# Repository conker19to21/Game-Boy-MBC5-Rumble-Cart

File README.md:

# Game Boy MBC5 Cartridge

This is a flashable MBC5-rumble based single cart for the Game Boy.

I had adapted the DC rumble motor to the board to allow the option to have rumble availability. This does NOT make non rumble based games have rumble feedback.

This board allows the option to allow both rumble and non rumble games in 1 cart with full save functionality!

Original files were converted from Eagle to KiCad cleaned and modified to add the changes.

Please note you will require either a Hot Air rework station or Hot Plate heating station to secure the DC motor properly to the board.

The Rumble feature is optional and if you decide not to use it exclude the following:

R2,
R3,
M1,
D1,
Q3

Battery hold down is NOT included however can be aquired at the following 2 links:

<a href="https://oshpark.com/shared_projects/XSjucPvH"> CR2Retainer</a>

<a href="https://www.digikey.com/short/4zrrw5rr"> RETAINER</a>

When installing D1 make sure it is in the correct orientation with diode line inside white boxed outline as seen in photo:

Special Thanks to Bucket Mouse, HDR and Bonzo!

Please see below for the Mouse's original documentation.

![image](https://private-user-images.githubusercontent.com/79350460/362808066-d0c1e5a3-aa70-49f6-8867-7be02a11127e.png?jwt=eyJhbGciOiJIUzI1NiIsInR5cCI6IkpXVCJ9.eyJpc3MiOiJnaXRodWIuY29tIiwiYXVkIjoicmF3LmdpdGh1YnVzZXJjb250ZW50LmNvbSIsImtleSI6ImtleTUiLCJleHAiOjE3MjUxNzgzNjYsIm5iZiI6MTcyNTE3ODA2NiwicGF0aCI6Ii83OTM1MDQ2MC8zNjI4MDgwNjYtZDBjMWU1YTMtYWE3MC00OWY2LTg4NjctN2JlMDJhMTExMjdlLnBuZz9YLUFtei1BbGdvcml0aG09QVdTNC1ITUFDLVNIQTI1NiZYLUFtei1DcmVkZW50aWFsPUFLSUFWQ09EWUxTQTUzUFFLNFpBJTJGMjAyNDA5MDElMkZ1cy1lYXN0LTElMkZzMyUyRmF3czRfcmVxdWVzdCZYLUFtei1EYXRlPTIwMjQwOTAxVDA4MDc0NlomWC1BbXotRXhwaXJlcz0zMDAmWC1BbXotU2lnbmF0dXJlPTA1MjI0NGZjN2M0MmQwMzY3ZTIxMTJkNjZlNmY0YThiMWQ0MDJiY2EwYzVjMDg4ZDA5NmZlMzE5MmU4ZjRjODkmWC1BbXotU2lnbmVkSGVhZGVycz1ob3N0JmFjdG9yX2lkPTAma2V5X2lkPTAmcmVwb19pZD0wIn0.tLwJES8k5k2GEA-q7z0vVUgHWVOFACCc68rWR7xbyPs)

This is my design of a flashable MBC5-based cartridge for the Game Boy. The MBC5 mapper greatly augments the memory access of the Game Boy for larger games. Most of the games that came out in the last years of the Game Boy and Game Boy Color used the MBC5 mapper.

This circuit board should cover most MBC5 games. The features are as follows:

- Able to make games up to 4 MB in size, that use up to 1 Mbit of RAM
- Compatibility with all four of the popular Game Boy battery management ICs - MM1026, MM1134, BA6129, and BA6735
- The option to add battery backup to the cartridge *without* the need of the original battery management ICs - perfect for MBC5 donors that didn't have batteries in them
- Fully compatible with the <a href="https://www.gbxcart.com/">GBxCart RW</a> so you can transfer games and save files to and from the board

All gerbers and source files can be found in this repo, as this project is fully open source. Technical documentation of the board can be found in the Technical folder.

## Important Things Before You Start

1) To use this board, you need to have an original Game Boy game that uses an MBC5 mapper chip. <a href="https://catskull.net/gb-rom-database/">You can find a list of games and their mappers here</a>. Use the search function. Please note the RAM is in bytes, not bits. Since SRAM in this repo is defined in bits, you need to convert by multiplying the number of bytes by 8.
2) You will need to remove the MBC5 from your donor cartridge for use on this board. This will require a hot air rework station or a hot plate. There's a list below of other parts you can re-use from the donor cartridge.
3) When soldering parts on, it's a good idea to put kapton tape or otherwise cover the bottom cartridge edge. You do not want to get solder on the cartridge contacts.
4) I am not responsible for any damage you do to your self or your property. Attempt this project at your own risk.
5) I do not guarantee design compatibility. You may encounter issues with certain games. There is also a chance I have made an error in the design or the BOM - if this is the case, I will do everything I can to address the problem as quickly as possible.
6) If you are using this board to make games other than for personal use, you must have permission from the originator to use and distribute any ROM images or other related material. You are responsible for making sure you adhere to any license requirements.

DO NOT use my circuit boards for profiting from stolen work - this especially includes homebrew content, ROM hacks, and using fan-made labels without permission from the originator. **Support original creators!**

## Board Characteristics and Order Information

The zipped folder contains all the gerber files for this board. The following options **must** be chosen when ordering boards for yourself.

- Thickness: 0.8mm
- Surface Finish: ENIG
- Gold Fingers: Yes, 30° chamfer

You can use the zipped folder at any board fabricator you like.

<a href="https://oshpark.com/shared_projects/T98aCJad">The board is also listed on OSH Park as well.</a> **Be sure to get them in 0.8mm thickness if you order from here.**

## Required Equipment

The EEPROMs on the board needs to be programmed somehow. I recommend using the GBxCart, as mentioned. These boards are fully compatible with it, and it makes reflashing games extremely easy using <a href="https://github.com/lesserkuma/FlashGBX">lesserkuma's FlashGBX software</a>.

Alternatively, you can buy an EEPROM programmer with a TSOP adapter. The downside to this method is that you have to desolder the chip every time you want to program it. The <a href="https://flashcatusb.com/">FlashcatUSB</a> is one popular option in retro spaces.

## Battery Safety

When assembling a board, I recommend populating all the parts *except* the battery, and getting it to run initially without it. This is to make it easier to fix any solder connections that might need fixing, without having to worry about getting the battery hot. And if you need to rework anything near the battery after you've put it on the board, be safe and remove it before putting a hot soldering iron next to it.

And this should go without saying, but if you're assembling these boards with a hot plate or hot air, *do not* solder the battery on this way. You should use an iron, and keep heat off of the battery as much as possible. 

(Also check polarity!)

## Board Configurations

The board comes with five sets of jumper pads for solder bridges. SJ1, SJ2, SJ3, and SJ4 require you to solder bridge the middle pad either to the left or right pads. SJ7 is configured by either leaving the pads unsoldered or bridging them with solder. Here are the situations where you need to add solder bridges.

### SRAM Size Selection (SJ1 and SJ2, or SW1)

These jumpers are located underneath the MBC5 chip, and labeled "64K" and "256K/1M". Solder them to configure the amount of RAM your cart uses. You must configure these pads for every game you make, unless you do not need RAM. <a href="https://catskull.net/gb-rom-database/">You can find a list of games here with their respective RAM sizes.</a>

- If the game you're making uses 256 Kbit or 1 Mbit of RAM, then solder the middle pads of the two jumper sets to the right pads.
- If the game you're making uses 64 Kbit of RAM, then solder the middle pads of the two jumper sets to the left pads.
- SJ1 and SJ2 must be soldered in the same direction.
- The footprint of these selection pads should allow for a DPDT switch, part number CAS-220A1, to be placed on these pads instead of having to bridge the pads with solder.

Note that you can make games that only require 64 Kbit of RAM and still use a 256 Kbit or 1 Mbit SRAM chip. You still need to configure the jumpers to the 64Kb setting, though.

**I recommend using 64 Kbit or 256 Kbit RAM chips, unless you absolutely need 1 Mbit for the game you are making.**

### Using an MM1134 or BA6735 for U4 (SJ3)

Bridge the jumper SJ3 if you have either an MM1134 or BA6735 for U4, specifically. Any other battery management IC must leave SJ3 unsoldered.

## Test Points and Final Checkout

On the back of the board are five test points. Here's where they are connected:

- TP1: SRAM supply voltage
- TP2: Battery voltage (after R1)
- TP3: Battery voltage (positive terminal of battery)
- TP4: Ground
- TP5: VCC input voltage

After you assemble your game, you should measure the current out of the battery. But first, you should program it with the GBxCart, or if you programmed the EEPROM separately, put it into a Game Boy and cycle power once. Then, flip the PCB upside down on a non-conductive surface (not your leg), and set your multimeter in DC millivolts (or volts). Put the positive probe on TP3 and the negative probe on TP2. If you used a 10kΩ for R1, as indicated in the BOM, you should read a voltage in the single of millivolts. If you have something much higher, especially voltages above 20mV, then you likely have an issue or short circuit on the board somewhere.

**Note: You need to power up the game at least once before battery currents will make sense - the battery management ICs can start up in an unknown state before applying main power to the board.**

To estimate battery life, see <a href="https://github.com/MouseBiteLabs/Game-Boy-MBC5-Cartridge/tree/main/Technical#estimating-battery-life">this section in the Technical Design Document</a>, or for more in-depth analysis, <a href="https://hackaday.io/project/11864-tritiled/log/72554-determining-maximum-runtime-176-to-202-years-cr2032">this Hackaday post</a>.

### Why not FRAM?

This board is only suitable for using SRAM. One downside to SRAM, if you haven't figured it out yet, is that you need a battery to keep the SRAM powered on even when the game is turned off. So eventually the battery will die, and your save data is lost. Some people have used FRAM, or Ferroelectric RAM, to keep save data around even after the battery dies (specifically, the popular part that's used for FRAM carts is the FM18W08). But, using this FRAM chip has a handful of downsides, and the benefit of keeping save data after the battery dies *in my opinion* does not outweigh the cons, which are as follows:

1) Quality, new stock, 5V tolerant FRAM is expensive ($12+ per part).
2) Cheaper FRAM chips from eBay or Aliexpress are notoriously flaky (anecdotally, ~50% success rate).
3) FRAM memory access requires different chip select timing than SRAM, and the Game Boy expects SRAM, so it is not natively compatible with FRAM carts. The Gameboy Color specifically cannot (easily) be made to properly access FM18W08 chip. You *can* use an OR gate and add the CLK on the cart edge to try to achieve the necessary timing, but it only works (properly) for DMG/MGB/SGB, not the GBC. It usually *works* in practice for GBC, but it's technically a datasheet violation and can potentially cause issues in edge cases. <a href="https://github.com/Gekkio">(Thanks to gekkio for pointing this out!)</a>

Brand new SRAM chips are ~$3, and having the SRAM footprint also allows you to use SRAM from an original cart if desired. You will *easily* get more than a decade of life running on a battery. You're already assembling this cartridge; you can dump the save and replace the battery before then!

Note that this isn't to throw shade at any FRAM-based carts, but for me personally, it's more trouble than it's worth. If you just *need* FRAM, you can find other cart designs out there that have it, <a href="https://github.com/HDR/MBC5-Flashcart">like this one!</a>

## Board Fitment

The shape of this board was originally meant to mimic original Game Boy circuit boards as closely as possible (v1.3 and earlier). Unfortunately, when placed in some aftermarket Game Boy cartridge shells (like those from Cloud Game Store), the circuit board has a lot of freedom to rotate around the main screw hole in the bottom-middle of the cartridge. This can cause misalignment when you put it in a Game Boy, which can cause a game to either not load properly (garbled Game Boy logo) or shut off the Game Boy because of a short circuit. This isn't *dangerous* or anything, just annoying.

In order to make the boards fit nicer in any kind of shell, for v1.4 I added extended tabs of circuit board material to the edges of the cartridges to keep it from rotating too much in shells, which was suggested to me by <a href="https://github.com/orangeglo">orangeglo</a>! (Thanks!)

If you're having trouble fitting the circuit board into a shell, because the tabs interfere with the cart edges, you can safely sand or trim them down as there is no copper within the tabs themselves. The only shell that appears to require any kind of trimming are Kitsch-Bent shells.

## Bill of Materials (BOM)

Your parts list will vary depending on the game you are trying to make, and what chips you have for the battery management (if any). **You cannot use both U4 and U5 - you must choose one or the other.** U4 comes from a donor cartridge, and U5 is a readily available aftermarket option.

Please carefully review the parts you need for the board you are trying to make. Do not add any parts to your build that don't appear in the column for the game you are making. This means you *cannot* populate every component on the board at the same time.

| Reference Designators | Value/Part Number              | Package          | Description        | No save carts | Save carts with MM1134 or BA6735 | Save carts with MM1026 or BA6129 | Save carts without donor U4 chip | Source                                           |
| --------------------- | ------------------------------ | ---------------- | ------------------ | ------------- | -------------------------------- | -------------------------------- | -------------------------------- | ------------------------------------------------ |
| B1                    | CR2032, CR2025, CR2016         | CR2032           | Backup Battery     |               | X                                | X                                | X                                | [https://mou.sr/3SeAzfT](https://mou.sr/3SeAzfT) |
| C1                    | 0.1uF                          | 0603             | Capacitor (MLCC)   | X             | X                                | X                                | X                                | [https://mou.sr/3ENc15O](https://mou.sr/3ENc15O) |
| C4                    | 0.1uF                          | 0603             | Capacitor (MLCC)   | X             | X                                | x                                |                                  | [https://mou.sr/3ENc15O](https://mou.sr/3ENc15O) |
| C5                    | 0.1uF                          | 0603             | Capacitor (MLCC)   |               | X                                | X                                | X                                | [https://mou.sr/3ENc15O](https://mou.sr/3ENc15O) |
| C6                    | 10uF                           | 0603             | Capacitor (MLCC)   |               | X                                | X                                | X                                | [https://mou.sr/3mZtSkF](https://mou.sr/3mZtSkF) |
| C7                    | 0.1uF                          | 0603             | Capacitor (MLCC)   | X             | X                                | X                                | X                                | [https://mou.sr/3ENc15O](https://mou.sr/3ENc15O) |
| C8                    | 0.1uF                          | 0603             | Capacitor (MLCC)   |               |                                  |                                  | X                                | [https://mou.sr/3ENc15O](https://mou.sr/3ENc15O) |
| Q1                    | 2N7002                         | SOT-23           | N-Channel FET      |               |                                  |                                  | X                                | [https://mou.sr/3rgfh6J](https://mou.sr/3rgfh6J) |
| Q2                    | 2N7002                         | SOT-23           | N-Channel FET      |               |                                  | X                                |                                  | [https://mou.sr/3rgfh6J](https://mou.sr/3rgfh6J) |
| Q3                    | SN74AHC1G126                   | SC70             | NPN FET            | X             | X                                | X                                | X                                | [https://mou.sr/3YlwRnW](https://mou.sr/3YlwRnW) OR <a href="https://www.aliexpress.com/item/1005005140909500.html?spm=a2g0o.order_list.order_list_main.5.637818020QcNX1"> AliExpress</a>|
| R1                    | 10k                            | 0603             | Resistor           |               | X                                | X                                | X                                | [https://mou.sr/3riR7IH](https://mou.sr/3riR7IH) |
| R2                    | 15Ω                            | 0603             | Resistor           | X             | X                                | X                                | X                                | [https://mou.sr/3zYvyRE](https://mou.sr/3zYvyRE) OR <a href="https://www.aliexpress.us/item/2251832678021377.html?spm=a2g0o.order_list.order_list_main.68.31621802J8yZUJ&gatewayAdapt=glo2usa4itemAdapt"> AliExpress</a>|
| R3                    | 30k                            | 0603             | Resistor           | X             | X                                | X                                | X                                | [https://mou.sr/46kfpCa](https://mou.sr/46kfpCa) OR <a href="https://www.aliexpress.us/item/2251832678021377.html?spm=a2g0o.order_list.order_list_main.68.31621802J8yZUJ&gatewayAdapt=glo2usa4itemAdapt"> AliExpress</a>||
| R7                    | 10k                            | 0603             | Resistor           |               |                                  | X                                |                                  | [https://mou.sr/3riR7IH](https://mou.sr/3riR7IH) |
| R8                    | 10k                            | 0603             | Resistor           | X             | X                                | X                                | X                                | [https://mou.sr/3riR7IH](https://mou.sr/3riR7IH) |
| R9                    | 130k                           | 0603             | Resistor           |               |                                  |                                  | X                                | [https://mou.sr/3MjXliy](https://mou.sr/3MjXliy) |
| R10                   | 49.9k                          | 0603             | Resistor           |               |                                  |                                  | X                                | [https://mou.sr/3Q3NRZO](https://mou.sr/3Q3NRZO) |
| U1                    | 29F016, 29F032, 29F033         | TSOP-48, TSOP-40 | Flash EEPROM       | X             | X                                | X                                | X                                | AliExpress or eBay                               |
| U2                    | MBC5                           | QFP-32           | MBC5 Mapper        | X             | X                                | X                                | X                                | Donor MBC5 Game Boy cartridge                    |
| U3                    | AS6C6264, AS6C62256, AS6C1008  | SOP-28, SOP-32   | SRAM               |               | X                                | X                                | X                                | [https://mou.sr/3ZxG6jd](https://mou.sr/3ZxG6jd) |
| U4                    | MM1026, MM1134, BA6129, BA6735 | SOIC-8           | Battery Management |               | X                                | X                                |                                  | Donor Game Boy cartridge                         |
| U5                    | TPS3613                        | MSOP-10          | Battery Management |               |                                  |                                  | X                                | https://mou.sr/45Ir2kh                           |
| M1                    | Vibration Motor                | Z43              | DC Motor           | X             | X                                | X                                | X                                | <a href="https://www.aliexpress.com/item/32787320737.html"> AliExpress</a>|
| D1                    |BC817-40                        | SOD-123          | Schottky diode     | X             | X                                | X                                | X                                | [https://mou.sr/3LEXYCJ](https://mou.sr/3LEXYCJ) OR <a href="https://www.aliexpress.com/item/1005003618692669.html?spm=a2g0o.order_list.order_list_main.5.31621802J8yZUJ"> AliExpress</a>|

*Note that C9 - C11 footprints are only included on the board for strange edge cases that may require them sometime in the future; do not populate! See the technical design document for more information.*

### Usable Donor Cartridge Parts

You can use a few parts from the donor cart on the new board to save some money. Note that you will generally get better reliability with new parts as opposed to old ones. For example: I have seen failed RAM chips from donors in the past.

1) **U2: MBC5** - This one is required
2) **U3: SRAM** - You can use this part *only if* the game you're making uses the same or less amount of RAM that the donor cartridge does
3) **U4: Battery Management IC** - Using this is probably preferred over the TPS3613 because it'll save you money and parts to put on

You could probably transfer over most of the 0.1uF capacitors but they're pretty cheap anyway, so I generally just recommend buying new resistors and capacitors.

### Capacitors C9 to C11

If you want to experiment with the capacitors C9 to C11, see this info below. **Be aware that adding these components in some of my tests actually ***stopped*** games from working, so again, assume that if you have a problem it lies elsewhere first, because it almost certainly does.**
- C9 is a capacitor connected nearby the SRAM's /WE pin to GND. These were populated on some cartridges, and I believe have a value of approximately 1 nF (0.001 uF) based on measurements from an MBC1 board that used it.
- C10 is a capacitor connected from the cart edge /RESET pin to GND. A spot for this capacitor was included on some MBC5 carts, but I cannot locate an instance of it actually being used when looking through the gbhwdb. I don't actually know what value this capacitor would need to be, so I am guessing 1 nF.
- C11 is a capacitor that I have added that was not used on any original Game Boy board. It connects to the SRAM's /CE pin, bypassing to GND. I have added this in the event incompatibilities arise with newer SRAM chips that have much faster speeds than older SRAM chips. This was a problem I encountered on some of my NES cartridges, so this is here just in case, but I have not found an instance where it's required.

## Things to Remember

- The footprint for the EEPROM is specifically for 29F016 - it has 48 pins. However, 29F032 and 29F033 are only 40 pin devices. They still work fine on the board though - place them in the center of the footprint, and leave the outer two pins on each corner empty
- The 29F016, 29F032, and 29F033 have been known to occasionally be defective upon arrival. They're either used, or new old stock, and usually only available from AliExpress.
- The footprint for the battery can fit a CR2032, CR2025, or CR2016 with solder tabs. The only difference is the mAh capacity (larger number = longer life). If you get Panasonic tabbed batteries, you may have to trim the battery tabs to make them fit on the footprint.
  - For untabbed coin cells, you can find battery retainer adapters online, <a href="https://retrogamerepairshop.com/products/hdr-game-boy-game-battery-retainer?variant=40511013290156">like this one,</a> but only for board revision v1.4. It will not fit on earlier revisions.
- For battery management, use either U4 *or* U5 and supporting components. **Do not** use U4 and U5 simultaneously on one board. They will interfere with each other.
- Generally, ROM sizes are conveyed in terms of kilo**bytes** and mega**bytes** (KB, MB). RAM size is usually conveyed in terms of kilo**bits** or mega**bits** (Kbit, Mbit). You can convert Kbit and Mbit to KB and MB by dividing Kbit or Mbit by 8. For example, 256 Kbit = 32 KB.
- You only need to provide ROM and RAM chips that have at least *or greater* the size of the game you are trying to make. That means you can use a 256 Kbit SRAM chip for a game that only requires 64 Kbit of RAM!

## Labels

If you want a Bucket Mouse branded label for your cartridge, look no further than <a href="https://krizdingus.com/mousebitelabs/">krizdingus's designs</a>. Special thanks to Kris for designing these, they look awesome! (If you are going to order/print these, use the high-res images hosted on his website, and *keep the labels for personal or non-commercial use only.*)

## Resources and Acknowledgements

- <a href="http://www.devrs.com/gb/files/hardware.html">Jeff Frohwein's GameBoy Tech Page</a>
- <a href="https://gbhwdb.gekkio.fi/">Game Boy Hardware Database</a>
- <a href="https://catskull.net/gb-rom-database/">Nintendo Gameboy Game List</a>
- <a href="https://www.gbxcart.com/">insideGadgets discord server for GBxCart RW compatibility requirements</a>
- <a href="https://github.com/lesserkuma/FlashGBX">Lesserkuma's FlashGBX software</a>
- <a href="https://www.alldatasheet.com/datasheet-pdf/pdf/99104/MITSUBISHI/MM1026.html">System Reset IC Datasheet</a>
- <a href="https://www.ti.com/lit/ds/symlink/tps3613-01.pdf?HQS=dis-mous-null-mousermode-dsf-pf-null-wwe&ts=1698238885366&ref_url=https%253A%252F%252Feu.mouser.com%252F">TPS3613 Datasheet</a>
- Board outline modified from <a href="https://tinkerer.us/projects/homebrew-gameboy-cartridge.html">Dillon Nichols's Homebrew Gameboy Cartridge project</a>
- Thanks to <a href="https://github.com/orangeglo">orangeglo</a> for his suggestion of adding spacers around the board edge for better fitment in aftermarket cartridges
- Some components from <a href="https://github.com/adafruit/Adafruit-Eagle-Library">Adafruit's Eagle parts library</a>
- Some components from <a href="https://www.snapeda.com/">SnapMagic</a>
- Thank you to <a href="https://github.com/Gekkio">gekkio</a> for their deep Game Boy knowledge resources, and for collaboration in demystifying some of the design choices on Game Boy cartridges
- Thanks to the awesome members of the <a href="https://moddedgameboy.club/">Modded Gameboy Club</a> for their feedback and support during the entire project development

## License

<br />This work is licensed under a <a rel="license" href="http://creativecommons.org/licenses/by-sa/4.0/">Creative Commons Attribution-ShareAlike 4.0 International License</a>. You are able to copy and redistribute the material in any medium or format, as well as remix, transform, or build upon the material for any purpose (even commercial) - but you **must** give appropriate credit, provide a link to the license, and indicate if any changes were made.

©MouseBiteLabs 2023

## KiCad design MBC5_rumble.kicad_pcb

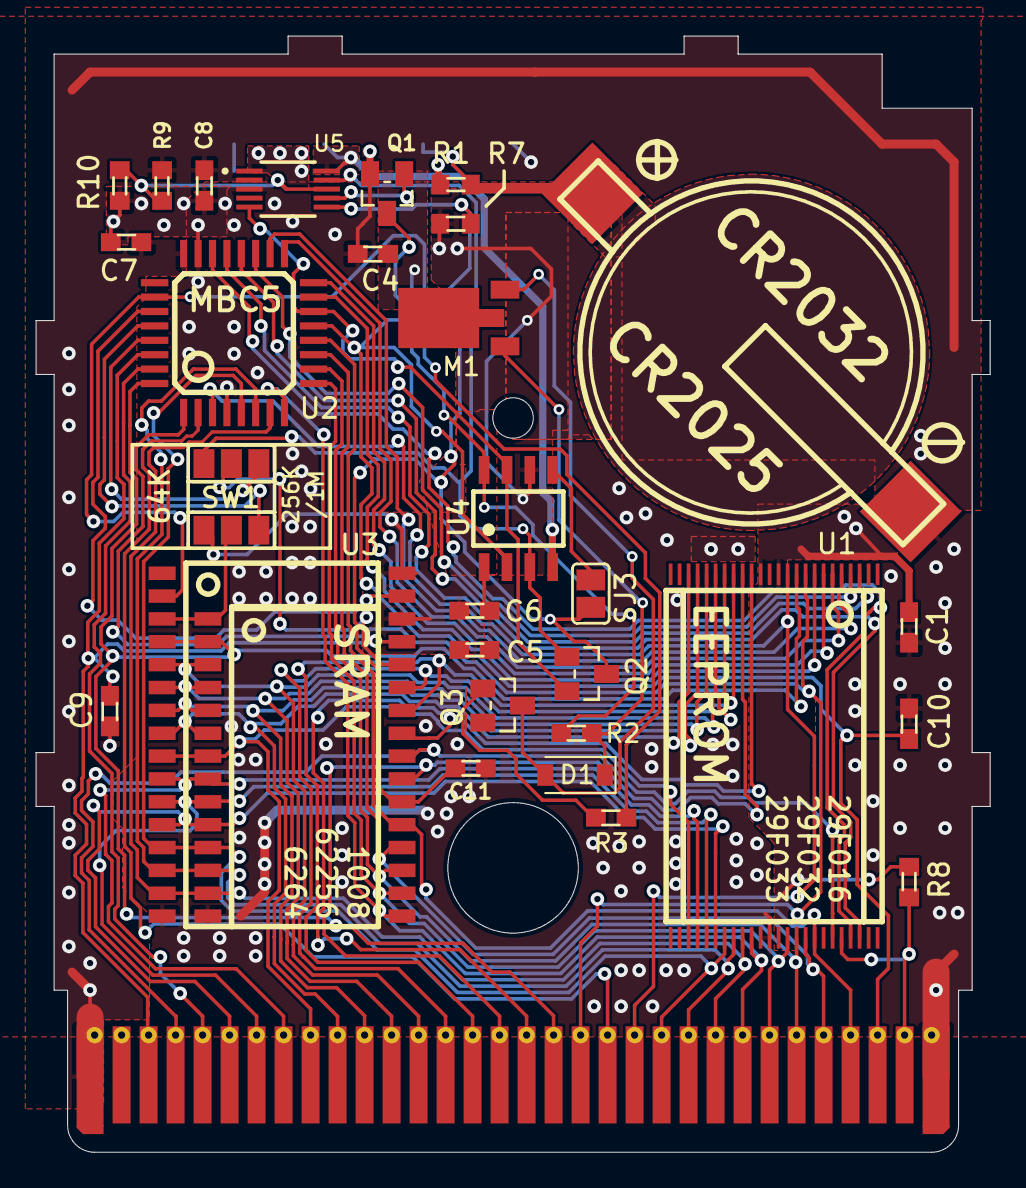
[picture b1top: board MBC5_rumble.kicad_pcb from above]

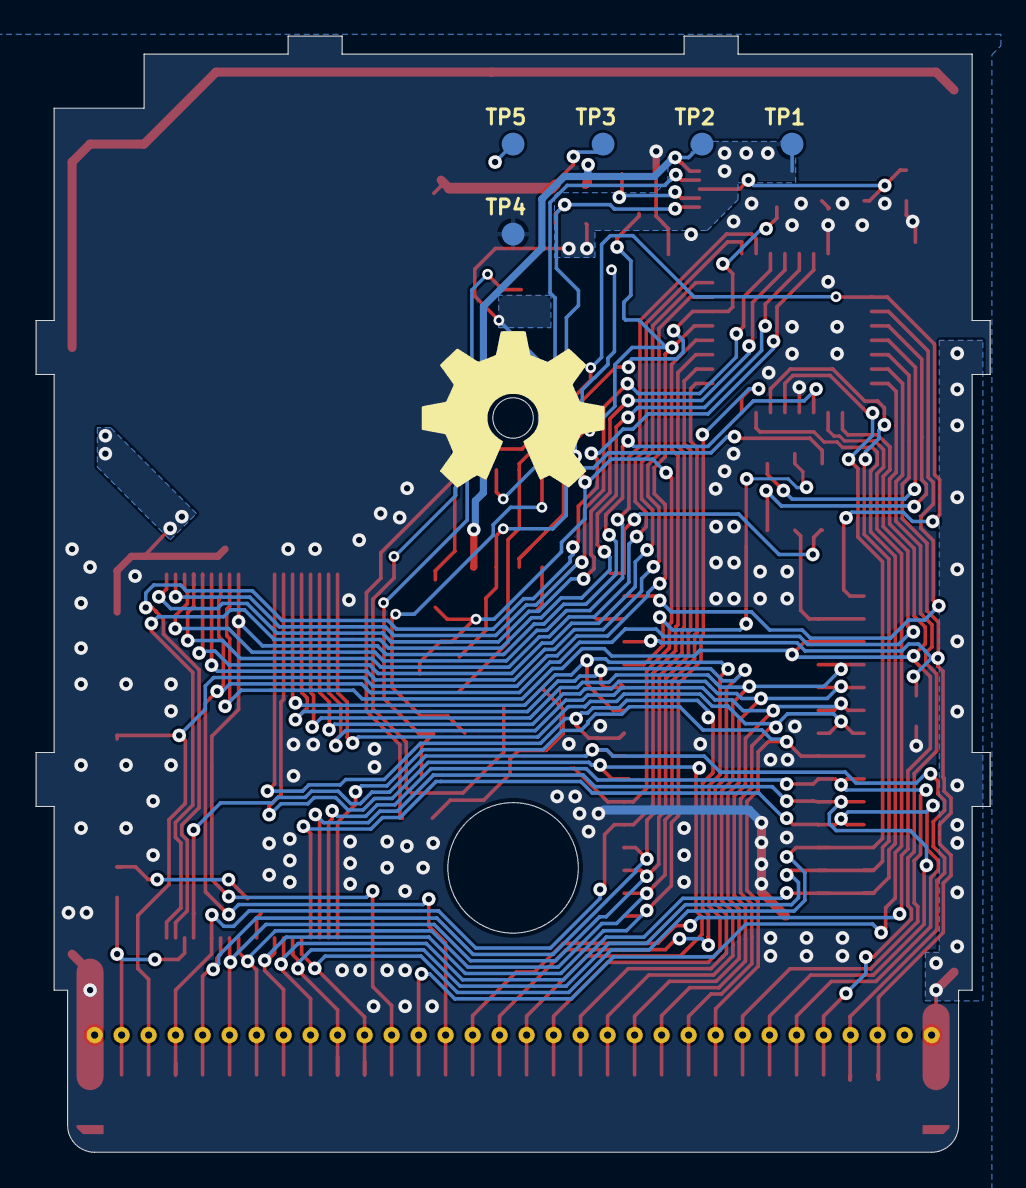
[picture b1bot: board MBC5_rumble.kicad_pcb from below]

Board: 2 copper layers, 53.0 x 62.0 mm, 33 parts (5 on the bottom side), 54 nets.

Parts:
B1: CR2025
C1, C4, C5, C7, C8: 0.1uF; C0603_334
C6: 10uF; C0603_334
C9, C10, C11: 0.001uF; C0603_334
D1: D; D_SOD-123
M1: Motor_DC; ANDA-T1035_vib_motor
P1: GBC_CART_TABBED
Q1, Q2: 2N7002; SOT23
R1, R7, R8, R9, R10: R0603
SJ1, SJ2: SJ_2
SJ3: SJ
TP1, TP2, TP3, TP4, TP5: TPB1,27; B1,27_385
U1: 29F016; TSOP-48
U2: QFP-32
U3: SO32L_L
U4: MM1134; SOIC-8
U5: TPS3613; MSOP-10

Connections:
/A0: P1.6 (A0), U1.30 (A0), U3.12 (A0), U3.L12 (A0)
/A1: P1.7 (A1), U1.29 (A1), U3.11 (A1), U3.L11 (A1)
/A2: P1.8 (A2), U1.28 (A2), U3.10 (A2), U3.L10 (A2)
/A3: P1.9 (A3), U1.27 (A3), U3.9 (A3), U3.L9 (A3)
/A4: P1.10 (A4), U1.22 (A4), U3.8 (A4), U3.L8 (A4)
/A5: P1.11 (A5), U1.21 (A5), U3.7 (A5), U3.L7 (A5)
/A6: P1.12 (A6), U1.20 (A6), U3.6 (A6), U3.L6 (A6)
/A7: P1.13 (A7), U1.19 (A7), U3.5 (A7), U3.L5 (A7)
/A8: P1.14 (A8), U1.18 (A8), U3.27 (A8)
/A9: P1.15 (A9), U1.17 (A9), U3.26 (A9)
/A10: P1.16 (A10), U1.16 (A10), U3.23 (A10)
/A11: P1.17 (A11), U1.15 (A11), U3.25 (A11)
/A12: P1.18 (A12), U1.10 (A12), U2.32 (A12), U3.4 (A12), U3.L4 (A12)
/A13: P1.19 (A13), U1.9 (A13), U2.1 (A13)
/A14: P1.20 (A14), U2.2 (A14)
/A15: P1.21 (A15), U1.11 (~CE), U2.3 (A15)
/AA13: SJ1.3, U2.29 (AA13)
/AA14: SJ2.3, U2.28 (AA14)
/AA15: U2.27 (AA15), U3.31 (A15)
/AA16: U2.26 (AA16), U3.2 (A16)
/CS_OUT: Q2.1 (G), SJ1.1, U4.3 (CS), U5.9 (~RESET)
/D0: P1.22 (D0), U1.31 (D0), U2.5 (D0), U3.13 (I/O0), U3.L13 (I/O0)
/D1: D1.2 (A), M1.2 (-), P1.23 (D1), U1.32 (D1), U2.6 (D1), U3.14 (I/O1), U3.L14 (I/O1)
/D2: P1.24 (D2), U1.33 (D2), U2.7 (D2), U3.15 (I/O2), U3.L15 (I/O2)
/D3: P1.25 (D3), U1.34 (D3), U2.8 (D3), U3.17 (I/O3)
/D4: P1.26 (D4), U1.38 (D4), U2.9 (D4), U3.18 (I/O4)
/D5: P1.27 (D5), U1.39 (D5), U2.10 (D5), U3.19 (I/O5)
/D6: P1.28 (D6), U1.40 (D6), U2.11 (D6), U3.20 (I/O6)
/D7: P1.29 (D7), U1.41 (D7), U2.12 (D7), U3.21 (I/O7)
/GND: B1.-, C1.2, C4.2, C5.2, C6.2, C7.2, C8.2, C9.2, C10.2, C11.2, P1.32 (GND), Q1.2 (S), R10.2, TP4.TP, U1.35 (GND), U1.36 (GND2), U2.4 (GND4), U2.23 (GND23), U3.16 (VSS), U3.L16 (VSS), U4.1 (GND), U5.3 (GND)
/RA14: U1.8 (A14), U2.15 (RA14)
/RA15: U1.7 (A15), U2.16 (RA15)
/RA16: U1.6 (A16), U2.17 (RA16)
/RA17: U1.5 (A17), U2.18 (RA17)
/RA18: U1.4 (A18), U2.19 (RA18)
/RA19: U1.3 (A19), U2.20 (RA19)
/RA20: U1.46 (A20), U2.21 (RA20)
/RA21: U1.45 (NC), U2.22 (RA21)
/RAM_/CS: Q2.2 (S), U2.14 (~RAM_CS), U4.7 (~Y), U5.5 (~CEIN)
/RAM_/CS_G: C11.1, Q2.3 (D), R7.1, SJ3.2, U3.22 (~CS), U5.6 (~CEOUT)
/SND: P1.31 (SND), R8.2, U1.44 (~WE)
/SRAM_SEL1: SJ1.2, U3.28 (A13)
/SRAM_SEL2: SJ2.2, U3.3 (A14), U3.L3 (A14)
/VBAT: R1.1, TP2.TP, U4.4 (VBAT), U5.10 (VBAT)
/VCC: C1.1, C4.1, C7.1, C8.1, D1.1 (K), M1.1 (+), P1.1 (VCC), R8.1, R9.1, TP5.TP, U1.12 (VCC), U1.14 (~RESET), U1.37 (VCC2), U2.24 (VCC), U4.8 (VCC), U5.2 (VDD)
/VCC_SRAM: C5.1, C6.1, R7.2, SJ2.1, TP1.TP, U3.30 (CS2), U3.32 (VCC), U4.6 (VOUT), U5.1 (VOUT)
//CS: P1.5 (~CS), U2.31 (~CS)
//RD: P1.4 (~RD), U1.43 (~OE), U3.24 (~OE)
//RST: C10.1, P1.30 (~RST), Q1.3 (D), U2.13 (~RESET), U4.2 (~RESET)
//WR: C9.1, P1.3 (~WR), U2.30 (~WR), U3.29 (~WE)
unnamed: B1.+, R1.2, TP3.TP
unnamed: Q1.1 (G), U5.7 (RESET)
unnamed: SJ3.1, U4.5 (~CS)
unnamed: R9.2, R10.1, U5.8 (SENSE)

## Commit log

2024-09-03 Rename MBC5_1-4.kicad_pro to MBC5_rumble.kicad_pro

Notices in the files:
README.md:
This work is licensed under a Creative Commons Attribution-ShareAlike 4.0 International License. You are able to copy and redistribute the material in any medium or format, as well as remix, transform, or build upon the material for any purpose (even commercial) - but you **must** give appropriate credit, provide a link t
©MouseBiteLabs 2023
